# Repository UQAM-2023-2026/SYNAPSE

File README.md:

# SYN/APSE  
**Cohorte UQAM Médias Interactifs 2023-2026**

> _Explorer un écosystème du futur, où chaque geste humain nourrit un réseau vivant et lumineux._  

---

## 🌿 Introduction  

**SYN/APSE** est une installation interactive et collective qui invite le public à explorer un écosystème symbiotique inspiré des **réseaux mycorhiziens** — ces structures souterraines où racines et champignons échangent énergie et informations.  

L’œuvre se déploie en deux niveaux — **la Canopée (haut)** et **le Mycélium (bas)** — où les participant·es interagissent à l’aide d’**objets-racines** connectés.  
Chaque geste contribue à la **“communergie”** : un flux d’énergie collective qui illumine, transforme et fait croître un monde partagé.  

SYN/APSE explore les notions de **collaboration, équilibre écologique, espoir et futurité**, à travers une approche **low-tech, écologique et sensible** mêlant art, biologie, design et technologie interactive.

---

## 🧩 Concept et expérience  

### Gestes fondamentaux  
- **Récolter** — capter l’énergie à travers l’exploration et la présence.  
- **Transférer** — échanger cette énergie entre personnes ou systèmes.  
- **Déposer** — redonner à l’écosystème pour le nourrir collectivement.  

### Parcours utilisateur  
1. **Entrée dans la Canopée** : un espace lumineux et sonore où les racines réagissent à la présence.  
2. **Exploration et recharge** : en manipulant l’objet-racine, le public accumule de l’énergie via la lumière et le mouvement.  
3. **Connexion avec autrui** : deux participant·es peuvent rapprocher leurs racines pour amplifier leur énergie commune.  
4. **Dépôt dans un nœud** : l’énergie récoltée est transférée, activant un effet lumineux et sonore dans l’environnement.  
5. **Propagation** : le réseau s’illumine, des bourgeons apparaissent, les sons se multiplient — le monde se régénère.  

Chaque interaction révèle un cycle de **photosynthèse et d’échange**, symbolisant la coopération plutôt que la compétition.

---

## 💡 Technologies  

| Domaine | Outils et technologies |
|----------|-----------------------|
| **Interactivité** | Capteurs infrarouges, transducteurs de surface, objets magnétiques connectés |
| **Lumière & projection** | Bandes LED, EL-Wire, projecteurs mapping |
| **Son** | Transducteurs sonores et ambiance évolutive |
| **Vision & capture** | Raspberry Pi, caméras et traitement d’image (OpenCV, scikit-image) |
| **IA & générativité** | Réseaux neuronaux pour formes visuelles et rétroaction sensorielle |
| **Logiciels** | TouchDesigner, Python, MaxMSP, Ableton Live |

> _L’installation combine art génératif, code créatif et dispositifs physiques réemployés, afin de limiter son empreinte écologique._

---

## ⚙️ Structure du dépôt  

```
SYN/APSE/
├─ docs/                      # Documentation projet
│  ├─ onboarding/             # Guides pour nouveaux arrivants
│  ├─ methodology/            # Méthodologie, décisions, RACI, etc.
│  └─ architecture/           # Diagrammes (Mermaid, PNG, PDF)
├─ src/                       # Code source (TouchDesigner, Python, etc.)
│  ├─ touchdesigner/
├─ assets/                    # Images, logos, polices
├─ hardware/                  # Schémas, BOM, STL, DXF, gerbers
├─ data/                      # Données (échantillons) — petites tailles
├─ scripts/                   # Outils dev/ops (build, export, sync)
├─ env/                       # Environnements
│  └─ environment.yml         # (renommer PF.yaml)
└─ README.md

```

---

## 🧠 Objectifs  

- Créer un **écosystème interactif** fondé sur la symbiose et l’équilibre collectif.  
- Favoriser une **expérience poétique et éducative** autour du vivant et du numérique.  
- Expérimenter un **design éthique** : matériaux réutilisés, inclusion, accessibilité.  
- Développer un **projet interdisciplinaire** où artistes, programmeur·euses et designers collaborent sur un même système vivant.  

---

## ♻️ Éthique et durabilité  

- **Réemploi** : priorité au matériel déjà existant.  
- **Accessibilité** : participation ouverte à tous.tes, sans barrière technologique.  
- **Équité et diversité** : représentation inclusive dans le concept et la production.  
- **Écologie** : conception à faible impact, matériaux biodégradables et recyclables.  

---

## 🧑‍🤝‍🧑 Équipe  

**Cohorte Médias Interactifs 2023-2026 – UQAM**  

---

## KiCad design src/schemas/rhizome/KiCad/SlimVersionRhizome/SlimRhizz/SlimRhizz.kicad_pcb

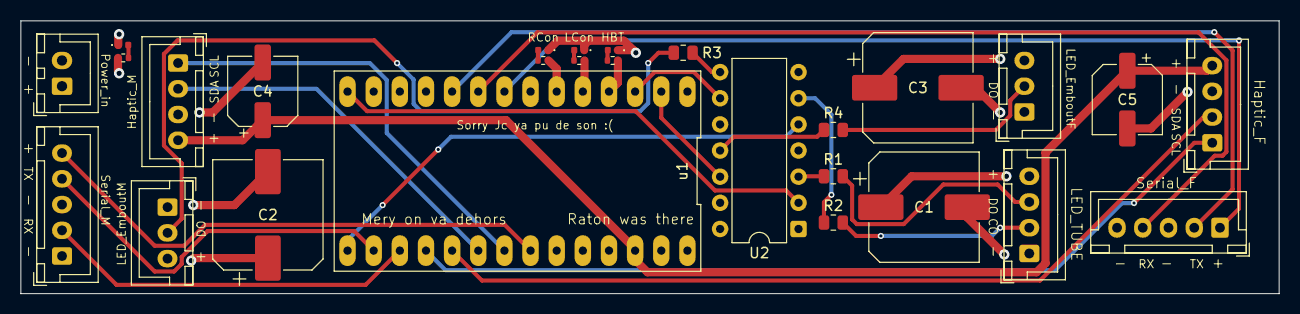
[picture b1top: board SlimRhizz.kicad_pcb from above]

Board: 4 copper layers, 122.2 x 26.5 mm, 27 parts (0 on the bottom side), 32 nets.

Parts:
C1, C2, C3: 1000uf; CP_Elec_10x10.5
C4, C5: 100uf; CP_Elec_6.3x5.4
D1: PWR; LED_0402_1005Metric
HBT: HBT; LED_0402_1005Metric
J1: POWER_IN; JST_XH_B2B-XH-A_1x02_P2.50mm_Vertical
J2: WS2812_Tip1; JST_XH_B3B-XH-A_1x03_P2.50mm_Vertical
J3: WS2812_Tip2; JST_XH_B3B-XH-A_1x03_P2.50mm_Vertical
J4: APA102_Strip; JST_XH_B4B-XH-A_1x04_P2.50mm_Vertical
J5: Haptic_DRV1; JST_XH_B4B-XH-A_1x04_P2.50mm_Vertical
J6: Haptic_DRV2; JST_XH_B4B-XH-A_1x04_P2.50mm_Vertical
J7: Pogo_Male; JST_XH_B5B-XH-A_1x05_P2.50mm_Vertical
J8: Pogo_Female; JST_XH_B5B-XH-A_1x05_P2.50mm_Vertical
LCon: L-Connect; LED_0402_1005Metric
PWR: 1000; R_0402_1005Metric
R1, R2, R3, R4: 220; R_0805_2012Metric
R6, R7, R8: 330; R_0402_1005Metric
RCon: R-Connect; LED_0402_1005Metric
U2: 74AHCT125; DIP-14_W7.62mm
u1: Teensy4.0r0

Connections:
+5V: C1.1, C2.1, C3.1, J1.1, J2.3, J3.3, J4.4, PWR.2, U2.14 (VCC), u1.VIN
/APA_CLK_PRE: U2.2, u1.12 (12/MISO)
/APA_DATA_PRE: U2.5, u1.13 (13/SCK)
/LED_TIP1: U2.9, u1.1 (1/TX1)
/LED_TIP2: U2.12, u1.0 (0/RX1)
GND: C1.2, C2.2, C3.2, C4.2, C5.2, D1.1 (K), HBT.1 (K), J1.2, J2.1, J3.1, J4.1, J5.3, J6.3, J7.1, J7.3, J8.3, J8.5, LCon.1 (K), RCon.1 (K), U2.1, U2.4, U2.7 (GND), U2.10, U2.13, u1.GND
unnamed: D1.2 (A), PWR.1
unnamed: HBT.2 (A), R6.2
unnamed: LCon.2 (A), R7.2
unnamed: R8.2, RCon.2 (A)
unnamed: J2.2, R3.2
unnamed: J3.2, R4.2
unnamed: J4.2, R2.2
unnamed: J4.3, R1.2
unnamed: J5.1, u1.19 (19/A5/SCL)
unnamed: J5.2, u1.18 (18/A4/SDA)
unnamed: C4.1, C5.1, J5.4, J6.4, u1.3.3V (3V3_LO)
unnamed: J6.1, u1.16 (16/A2/RX4)
unnamed: J6.2, u1.17 (17/A3/TX4)
unnamed: J7.2, u1.15 (15/A1/RX3)
unnamed: J7.4, u1.14 (14/A0/TX3)
unnamed: J7.5, u1.20 (20/A6/TX5)
unnamed: J8.1, u1.6
unnamed: J8.2, u1.8 (8/TX2)
unnamed: J8.4, u1.7 (7/RX2)
unnamed: R1.1, U2.3
unnamed: R2.1, U2.6
unnamed: R3.1, U2.8
unnamed: R4.1, U2.11
unnamed: R6.1, u1.2
unnamed: R7.1, u1.3
unnamed: R8.1, u1.4

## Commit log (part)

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2025-12-02 rachel_infra_1er_dec
2025-12-02 bloup
2025-12-02 uuugh whe are there but also not really
2025-12-02 PCB V1 final ordered
2025-12-02 whats this?
2025-12-02 modelpoursarag
2025-12-02 travail sur le mur02
2025-12-02 INFRA_RACHEL_2DEC_TEST
2025-12-03 patch_global_testmenu_2dec
2025-12-03 ANTHOCHAMPI
2025-12-03 infra_rachzz_2dec_bonnenuit
2025-12-03 modifiactation
2025-12-03 basse noeud
2025-12-03 tentative de régler le serial
2025-12-03 aehaejkerfkjeaf
2025-12-03 bible study
2025-12-03 V1 de la communication inter Rhyzome
2025-12-04 Modèle 3D Rhizome V1
2025-12-04 more bible study
2025-12-04 I guess I somehow forgot one push
2025-12-05 slim Rhizz done
2025-12-05 I JUST PUSHED WTF
2025-12-05 travail visuels
2025-12-05 ajoutv4 patch global visuels
2025-12-05 V2_rhyzome
2025-12-05 Modele pour case EPS32-POE-ISO
2025-12-05 rachh_infra_5dec_pm
2025-12-05 v5 patch global visuel
2025-12-05 anthosupport
2025-12-05 Debut communication avec noeud
2025-12-05 rachh_infra_5DECELP
2025-12-06 qqun a touché a ma patch pis a push :(
2025-12-06 Add relocation note for backend patch
2025-12-06 on a les états, la respiration, les totaux, les sous-totaux
2025-12-06 stoopid teenzy plz just talk to me
2025-12-06 modif patch global visuels
2025-12-06 added DATA Tox qui se connecte au Mac
2025-12-07 gitignore DS Store
2025-12-07 if im not fixing this tonight im crashing out <3
2025-12-07 not happening tonight sorry kids...
2025-12-07 tentative de generation avec plus de 2 rhizomes
2025-12-07 ajout_update_chsampigon_visuel_patch_global
2025-12-07 give energy to node
2025-12-07 Update model
2025-12-07 rachhzz_infra_patchglobal_7dec
2025-12-07 rachzzz_reconfig_tox_7dec
2025-12-08 wtf is this
2025-12-08 rhizome et noeud besties 4 LIFE!
2025-12-08 fix communication rhizome/noeud
2025-12-08 ajout select patch global visuel
2025-12-08 updated DATA.tox
2025-12-08 data.tox reformat
2025-12-08 changed Port DATA
2025-12-08 changed data parsing
2025-12-08 fixed it
2025-12-08 mes lichens!
2025-12-08 gitignore
2025-12-09 fixed DATA.py Script
2025-12-09 RACH_BONMATIN
2025-12-09 fixed port
2025-12-09 encore ...
2025-12-09 ra_integration_data
2025-12-09 integ_visuel_alpha
2025-12-09 pre-general changes
2025-12-09 mes lichens pour la générale
2025-12-09 Create test
2025-12-09 rach_patch-globale_vizu
2025-12-09 gitignore pour mp4
2025-12-09 integration visuels lichens
2025-12-09 Création de branche et ajout de changements
    blablabla
2025-12-09 flower_visuel
2025-12-09 TCP-IP crashing main on pulse
2025-12-09 ds store
2025-12-09 Add MainControl_v4a.175.toe and update routing files
    Added new MainControl_v4a.175.toe file and updated MainControl_v4a.toe to latest version. Moved previous MainControl_v4a.174.toe to Backup directory. Updated .gitignore to ignore duplicate .DS_Store 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
2025-12-10 Sound is on github!!!
2025-12-10 alex - updated gitignore to ignore media folder
2025-12-10 Alpha
2025-12-10 general cancelled o7
2025-12-10 .tox v4 champi
2025-12-10 fixed??
2025-12-10 bouarh demo Rat
2025-12-10 push push babyy
2025-12-11 champi_modif
2025-12-11 fix intégration de la faille
2025-12-11 nouveau tox champi patch global
2025-12-11 updated DATA
2025-12-11 LastPushBeforeAlpha
2025-12-11 IT FUCKING WORKS
2025-12-11 PréGénéraléYé
2025-12-11 rachh_madmapp
2025-12-12 post-generale
2025-12-12 post-gen pt.II
2025-12-12 Vfinal avant alpha
2025-12-12 were all set babyyy
2025-12-12 miam
2025-12-12 lichens plus vite
2025-12-12 SOUND GUYZ
2025-12-12 PANIK
2025-12-16 Update PCB
2026-01-03 3 connecteur par noeud not tested
2026-01-08 Update PCB SlimRhizz
2026-01-12 changements dernière minute
2026-01-13 push 2026 (CAN BE REVERTED)
2026-01-13 Outils Organisation
2026-01-13 PCB Trace Width Fix
2026-01-15 patch_global_visuel
2026-01-15 file_path_visuel
2026-01-15 14janv_opt_visus
2026-01-15 pcb v2
2026-01-15 double serial
2026-01-15 ajout_visuel_pollen
2026-01-18 DOUBLE UART CHECKED
2026-01-19 womp womp triple but double is better
2026-01-19 infra_supra_19janv
2026-01-19 visuel_pollen
2026-01-19 visuel_pollen opacity
2026-01-20 merge_fleur_pollen_visuel
2026-01-20 suite visuel pollen
2026-01-20 debut animation led
2026-01-20 infra-sup_bye_19janv
2026-01-20 Created new versionning of backend
2026-01-20 moved stuff
2026-01-22 pollenv3
2026-01-22 infra_sup_21janv_bonnenuit
2026-01-22 update led noeud
2026-01-22 nouveau .tox pr esp
2026-01-22 better esp tox
2026-01-22 3d case 4 esp
2026-01-22 scéno
2026-01-22 32 stuff 4 esp
2026-01-23 more
2026-01-23 v2, v3 visuel pollen
2026-01-23 my mess
2026-01-23 v7 visuel_champi
2026-01-24 ajout_visuel_fleur_pollen
2026-01-24 integration_visuel
2026-01-25 update pour test lundi
2026-01-26 what is this
2026-01-26 connecteur
2026-01-26 modif_visuel_idle
2026-01-27 changing tactics
2026-01-27 esp bullshit
2026-01-27 fixed test
2026-01-27 random-replicator visuel
2026-01-27 v2 replicator_visuel
2026-01-27 visuel_projov4
2026-01-27 amelioration led tentative connexion noeud
2026-01-27 fucking pogopin a marde
2026-01-27 3d model conecct
2026-01-27 pollen vf visuel
2026-01-27 transition_pollen_visuel
2026-01-27 27fev_visus
2026-01-28 more work (it never stop)
2026-01-28 Sasha tu fait chier mes led :((
2026-01-28 réglééé
2026-01-28 séparation tox
2026-01-28 séparation noeud
2026-01-28 changed DATA tox for adding Node LEDs
2026-01-28 visuel_projo3_Vrach2_28jan
2026-01-29 fin sprint
2026-01-29 madmapper_visuel
2026-01-29 rara
2026-01-29 madmapper2_visuels_28_janv
2026-01-29 touch_data_28janv
2026-01-29 projo3V3Flo visuel
2026-01-29 pollen_level_visuel_pollen_vf_v2
2026-01-31 blob
2026-01-31 pollen v2 visuel opacité
2026-01-31 pollen v3 test opacité
2026-02-01 Double drainnrate in da house
2026-02-02 anim led (work in progress)
2026-02-02 Release
2026-02-02 pre-release changes (backup of old Backend)
2026-02-02 changed Values, refined Debug Mode, Added Params
2026-02-02 added Data
2026-02-02 added data exports
2026-02-02 v4 projo 3 visuel
2026-02-02 projo v4 visules flo
2026-02-02 projo 3 v4 flo visuel
2026-02-02 UI is insane now
2026-02-02 coloors
2026-02-03 patch_global_projo3_v4
2026-02-03 projo3v4_visuel
2026-02-03 v8_visuel
2026-02-03 visuel_projo3_v4
2026-02-03 pre-changes
2026-02-03 lundii hihi
2026-02-03 2fev_bonne_nuite_VISUALSINTEG
2026-02-03 did someone rename my stuff??
2026-02-03 dual drainrate FIXED
2026-02-03 UI fix (windows)
2026-02-03 teste
2026-02-03 UI Fix
2026-02-03 j'aime pas quand ça se renomme tout seul
2026-02-03 mac changes
2026-02-03 v9 champi_bleu
2026-02-04 more led
2026-02-04 UX changes
2026-02-04 fin journee lundi
2026-02-04 mapping rara
2026-02-04 ca rara
2026-02-04 v9_champi
2026-02-04 VIUEL
2026-02-05 TESTS MERCREDI
2026-02-05 TESTSS
2026-02-05 4fev_visuelVignes
2026-02-05 4fev_integ_tests
2026-02-05 fin journee mercredi nouveau design de code
2026-02-05 more led BLOUP
2026-02-05 more blip bloup
2026-02-05 vf4_pollen
2026-02-05 V4_PROJO_TOM
2026-02-06 visuel_8_pollen
2026-02-06 projo3_patch_global
2026-02-06 projo1_patch_global
2026-02-06 no comments
2026-02-08 portesouvertes
2026-02-09 downgrade people downgrade
2026-02-09 update son
2026-02-09 projo2_v5 visuel
2026-02-09 added mode nuit
2026-02-09 modif_nom_fichier_visuel
2026-02-10 fin journee, communication entre rhizome réglée
2026-02-10 rara studio
2026-02-10 ajout ndi_visuel_projo3
2026-02-10 correction_pollen_pacerelle
2026-02-11 code du noeud yer done asti
2026-02-11 LED NODE
2026-02-11 update_visuss
2026-02-11 modif_madmapper_visuel
2026-02-11 update_again
2026-02-11 madmapper_modif
2026-02-12 vignes_couleur
2026-02-12 modif communication et ajout led embout
2026-02-12 general rara
2026-02-12 ca bug
2026-02-12 MADMAPPER
2026-02-12 11/02
2026-02-12 update_visussss_soir
2026-02-12 update_tokyo2
2026-02-12 Visus_clean
2026-02-12 debug
2026-02-12 backend -- end of FEB11
2026-02-12 fin journée
2026-02-12 modif_pollen_optimisation
2026-02-12 pollen_vf5
2026-02-12 projo3_pollen
2026-02-12 mode_contemplatif
2026-02-12 integration_mode_contemplatif_projo3
2026-02-12 tox_mode_contemplatif_visuel
2026-02-12 sauvegarde
2026-02-12 projo2_integration_contemplatif_visuel
2026-02-13 module de simulation -- fallback
2026-02-13 update_bonne_nuit
2026-02-13 added simulationTOX with added funct. to give less to a state and more to the other
2026-02-13 ajout_contemplatif_projo1_visuel
2026-02-13 regler_bug_projo3_et1_visuel
2026-02-13 modif_projo1_et_3
2026-02-14 finalisation communication, led pour generale
2026-02-14 optimisation_visuel_projo3
2026-02-14 14 Feb Son
    Touch Animation update
2026-02-15 pre-generale
2026-02-16 rara generale
2026-02-16 code pour test utilisateurs
2026-02-16 visus_test16fev
2026-02-16 visus_update_final
2026-02-16 Visuel_Projo2
2026-02-16 optimisation_16fev
2026-02-16 i dunno man
2026-02-16 vigne_portail_16fev
2026-02-16 node
2026-02-16 Update son 15 Fevrier
    - fixed bug switch states saturation
2026-02-16 menage_dossier_visuel
2026-02-17 synapseeeeeeeeeeeee
2026-02-17 Tests utilisateurs
2026-02-18 test_utilisateur
2026-02-18 contemplatif_visuel
2026-02-18 regle_bug_visuel_contemplatif
2026-02-18 projo2_visuel
2026-02-18 visuel_projo1
2026-02-19 v2pacerelle_pollen
2026-02-19 visus_opt
2026-02-19 added plantation Réseautique
2026-02-19 projo3
2026-02-19 new version
2026-02-19 modifications haptic
2026-02-19 oublie
2026-02-19 VISUS-FIN_DU_EMERY
2026-02-19 bonn_nuit
2026-02-19 lien_tunel_tokyo3_visuel
2026-02-22 animsooon
2026-02-22 events
2026-02-22 visus_shit_acommit
2026-02-22 sceno
2026-02-22 pré-generale
2026-02-22 sceno_arduino
2026-02-22 update_fix_viz
2026-02-23 generale went well, still some soldering issues
2026-02-23 Correction_visuel_last_generale
2026-02-23 added Event Faker
2026-02-23 synapse_22fev_visu
2026-02-23 fallback code rhizome
2026-02-23 done
2026-02-23 added Extreme/Appel Faker Toggle
2026-02-23 23_fevrier_1h39_install_son
2026-02-23 visu_tom3
2026-02-25 rara energies mappé?
2026-02-26 animations
2026-02-26 bllah b;ah blaj
2026-02-26 ok man ça avance
2026-02-26 lastpush
2026-02-26 veille synapse
2026-02-26 EVENT DONE
2026-02-26 synapse ready??
2026-02-26 Post Generale Son 25 Fev 2026
2026-02-26 Synapse c LIVE son
2026-02-27 c liveeeeeeeee
2026-02-27 merging
2026-02-27 separation LEDS
2026-02-27 Backup avant expérimentations
2026-02-27 added backup
2026-02-27 2 noeuds infra -- 2 noeuds supra
2026-02-27 added fallback settings
2026-02-28 day-2 done
2026-02-28 fin day 2
2026-02-28 led separation
2026-02-28 update UX
2026-03-01 SYNAPSE - Post Nuit Blanche
2026-03-02 dont touch
2026-03-02 changement i guess
2026-03-02 visueltom
2026-03-02 dernier-push-visus
2026-03-02 push_lichen
2026-03-02 SYNAPSE is done
2026-03-03 last day son
2026-03-05 its the end
